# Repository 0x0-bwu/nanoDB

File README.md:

# nanoDB

A lightweight, high-performance database framework designed for Electronic Design Automation (EDA) applications.

**Status:** Under Active Development  
**License:** Non-commercial

## Overview

nanoDB is a modern C++ database framework specifically built for EDA workflows. It provides efficient data structures and interfaces for managing chip design data, including Liberty timing libraries, Verilog netlists, parasitic information, package models, and power analysis.

## Features

- **Liberty Library Support**: Parse and manage Liberty timing library files (.lib)
- **Verilog Support**: Handle Verilog netlist data structures
- **Chip Design Data**: Comprehensive chip design database with efficient storage
- **Package Modeling**: Support for package design and analysis
- **Parasitic Analysis**: Manage parasitic resistance and capacitance data
- **Power Analysis**: Power consumption calculation and optimization
- **Serialization**: Boost serialization support for database persistence
- **Thread-Safe**: Multi-threaded operations support with OpenMP
- **Memory Efficiency**: Optional jemalloc/tcmalloc support for optimized memory management

## Requirements

### System Requirements
- CMake 3.14 or higher
- C++23 compatible compiler:
  - GCC (recommended)
  - AppleClang (macOS)

### Dependencies

- **Boost** (1.83.0 or higher)
  - boost_serialization
- **Eigen3**: Linear algebra library
- **libpng**: PNG image support
- **OpenMP**: Parallel computing (optional)
- **jemalloc** or **tcmalloc**: Memory allocator (optional)

### Environment Variables

Set the `BOOST_PATH` environment variable to your Boost installation directory:
```bash
export BOOST_PATH=/path/to/boost
```

For custom Eigen installation, set:
```bash
export EIGEN_PATH=/path/to/eigen
```

## Building

### Basic Build

```bash
# Configure
cmake -Bbuild -G Ninja

# Build
cmake --build build
```

### Build Options

```bash
# Enable assertions
cmake -Bbuild -DENABLE_ASSERTION=ON

# Enable/disable exceptions
cmake -Bbuild -DENABLE_EXCEPTION=OFF

# Use jemalloc
cmake -Bbuild -DNS_MALLOC_LIB=jemalloc

# Use tcmalloc
cmake -Bbuild -DNS_MALLOC_LIB=tcmalloc

# Enable address sanitizer (for debugging)
cmake -Bbuild -DENABLE_ASAN=ON

# Enable thread sanitizer (for debugging)
cmake -Bbuild -DENABLE_TSAN=ON

# Enable profiling
cmake -Bbuild -DENABLE_PROFILING=ON

# Build without tests
cmake -Bbuild -DBUILD_NANO_TEST=OFF
```

### macOS Build

On macOS with Homebrew:
```bash
# Install dependencies
brew install boost eigen libpng cmake ninja

# Optional: Enable Apple Accelerate framework
cmake -Bbuild -DENABLE_APPLE_ACCELERATE=ON -G Ninja
cmake --build build
```

### Ubuntu/Debian Build

```bash
# Install dependencies
sudo apt-get update
sudo apt-get install build-essential cmake ninja-build \
    libeigen3-dev libpng-dev libjemalloc-dev

# Install Boost (or use install-boost action in CI)
# Build with jemalloc
export BOOST_PATH=/path/to/boost
cmake -Bbuild -DNS_MALLOC_LIB=jemalloc -G Ninja
cmake --build build
```

## Testing

Run the unit tests:
```bash
build/bin/nanoTest.exe
```

## Project Structure

```
nanoDB/
├── include/nano/          # Public headers
│   ├── db                 # Main database header
│   ├── core/              # Core module headers
│   │   ├── basic/         # Basic data structures
│   │   ├── chip/          # Chip design data
│   │   ├── liberty/       # Liberty library
│   │   ├── package/       # Package modeling
│   │   ├── parasitic/     # Parasitic data
│   │   ├── power/         # Power analysis
│   │   └── verilog/       # Verilog support
│   └── common/            # Common utilities
├── src/                   # Source code implementation
│   ├── basic/             # Database core implementation
│   ├── chip/              # Chip module
│   ├── liberty/           # Liberty parser and data structures
│   ├── package/           # Package module
│   ├── parasitic/         # Parasitic module
│   ├── power/             # Power module
│   └── verilog/           # Verilog module
├── test/                  # Unit tests
├── 3rdparty/             # Third-party dependencies
├── reference/            # Reference documentation
└── tools/                # Utility tools
```

## Usage

Include the main header in your C++ code:

```cpp
#include <nano/db>

// Use the nano namespace
using namespace nano;

// Create and use database objects
// (Detailed API documentation coming soon)
```

## Contributing

This project is currently under active development. Contributions, issues, and feature requests are welcome.

## License

**Non-commercial use only.** This software is provided for educational and research purposes.

## References

- Liberty User Guides and Reference Manual Suite (Version 2017.06) included in `reference/` directory

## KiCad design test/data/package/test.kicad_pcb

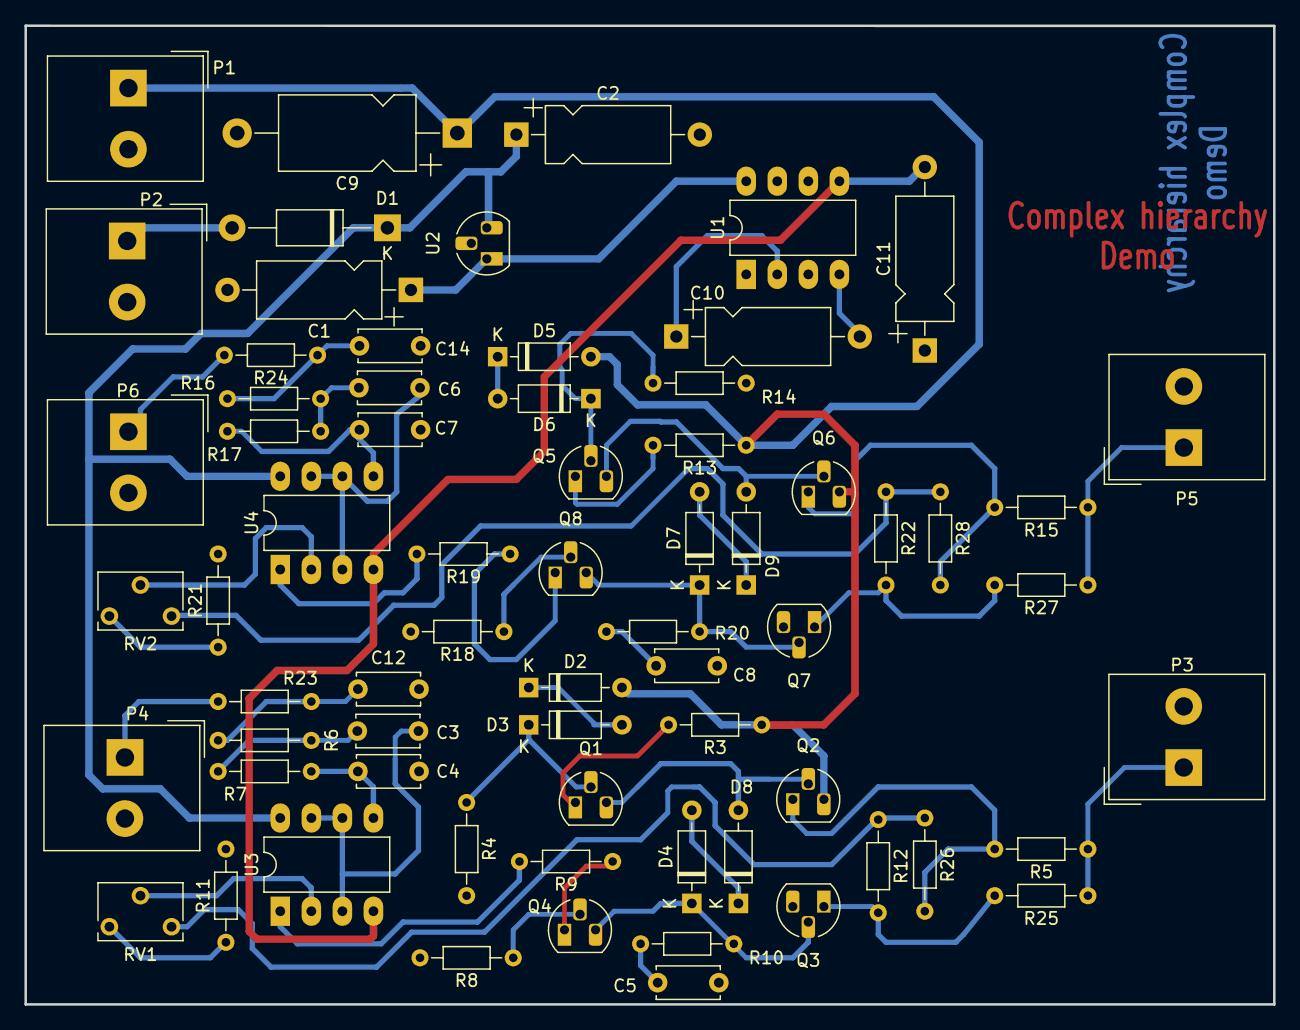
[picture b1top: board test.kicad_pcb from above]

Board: 2 copper layers, 102.1 x 80.0 mm, 68 parts (0 on the bottom side), 50 nets.

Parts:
C1: 47uF; CP_Axial_L10.0mm_D4.5mm_P15.00mm_Horizontal
C2: 47uF/20V; CP_Axial_L10.0mm_D4.5mm_P15.00mm_Horizontal
C3, C6: 15nF; C_Disc_D5.0mm_W2.5mm_P5.00mm
C4, C7: 4.7nF; C_Disc_D5.0mm_W2.5mm_P5.00mm
C5, C8: 820pF; C_Disc_D5.0mm_W2.5mm_P5.00mm
C9: 47uF/63V; CP_Axial_L11.0mm_D6.0mm_P18.00mm_Horizontal
C10, C11: 10uF; CP_Axial_L10.0mm_D4.5mm_P15.00mm_Horizontal
C12, C14: 150nF; C_Disc_D5.0mm_W2.5mm_P5.00mm
D1: 1N4007; D_DO-41_SOD81_P12.70mm_Horizontal
D2, D3, D4, D5, D6, D7, D8, D9: 1N4148; D_DO-35_SOD27_P7.62mm_Horizontal
P1, P2, P3, P4, P5, P6: CONN_2; Altech_AK300_1x02_P5.00mm_45-Degree
Q1, Q3, Q5, Q7: MPSA92; TO-92_HandSolder
Q2, Q4, Q6, Q8: MPSA42; TO-92_HandSolder
R3, R13: 470; R_Axial_DIN0204_L3.6mm_D1.6mm_P7.62mm_Horizontal
R4, R12, R14, R22, R26, R28: 220K; R_Axial_DIN0204_L3.6mm_D1.6mm_P7.62mm_Horizontal
R5, R15, R25, R27: 47; R_Axial_DIN0204_L3.6mm_D1.6mm_P7.62mm_Horizontal
R6, R7, R16, R17: 22K; R_Axial_DIN0204_L3.6mm_D1.6mm_P7.62mm_Horizontal
R8, R9, R18, R19, R23, R24: 1K; R_Axial_DIN0204_L3.6mm_D1.6mm_P7.62mm_Horizontal
R10, R20: 5,6K; R_Axial_DIN0204_L3.6mm_D1.6mm_P7.62mm_Horizontal
R11, R21: 4,7K; R_Axial_DIN0204_L3.6mm_D1.6mm_P7.62mm_Horizontal
RV1, RV2: 4,7K; Potentiometer_Bourns_3266W_Vertical
U1: ICL7660; DIP-8_W7.62mm_LongPads
U2: 78L05; TO-92_HandSolder
U3, U4: LM358N; DIP-8_W7.62mm_LongPads

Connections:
+12V: C2.1, D1.1 (K), U2.3 (VI), U3.8 (V+), U4.8 (V+)
-VAA: C11.2, U1.5 (VOUT), U3.4 (V-), U4.4 (V-)
/12Vext: D1.2 (A), P2.1
/ampli_ht_horizontal/PIEZO_IN: P6.1, R24.2
/ampli_ht_horizontal/PIEZO_OUT: P5.1, R15.1, R27.1
/ampli_ht_horizontal/S_OUT+: R22.1, R28.1, RV2.3
/ampli_ht_horizontal/Vpil_0_3,3V: C6.1, U4.3 (+), U4.6 (-), U4.7
/ampli_ht_vertical/PIEZO_IN: P4.1, R23.2
/ampli_ht_vertical/PIEZO_OUT: P3.1, R5.1, R25.1
/ampli_ht_vertical/S_OUT+: R12.1, R26.1, RV1.3
/ampli_ht_vertical/Vpil_0_3,3V: C3.1, U3.3 (+), U3.6 (-), U3.7
GND: C1.2, C2.2, C4.2, C5.2, C7.2, C8.2, C9.2, C11.1, C12.2, C14.2, P1.2 (PM), P2.2 (PM), P3.2 (PM), P4.2 (PM), P5.2 (PM), P6.2 (PM), Q3.3 (C), Q7.3 (C), R4.2, R8.2, R11.2, R14.2, R18.2, R21.2, U1.3 (GND), U2.2 (GND)
HT: C9.1, D2.2 (A), D5.2 (A), P1.1, Q2.3 (C), Q6.3 (C), R3.1, R13.1
unnamed: C3.2, R6.1, R7.2
unnamed: C5.1, R10.2
unnamed: C6.2, R16.1, R17.2
unnamed: C8.1, R20.2
unnamed: C12.1, R6.2, R23.1
unnamed: C14.1, R16.2, R24.1
unnamed: D2.1 (K), D3.2 (A)
unnamed: D3.1 (K), Q1.2 (B), R4.1
unnamed: D4.2 (A), D8.1 (K)
unnamed: D4.1 (K), Q3.2 (B), Q4.3 (C), R10.1
unnamed: D5.1 (K), D6.2 (A)
unnamed: D6.1 (K), Q5.2 (B), R14.1
unnamed: D7.2 (A), D9.1 (K)
unnamed: D7.1 (K), Q7.2 (B), Q8.3 (C), R20.1
unnamed: D8.2 (A), Q1.3 (C), Q2.2 (B)
unnamed: D9.2 (A), Q5.3 (C), Q6.2 (B)
unnamed: Q1.1 (E), R3.2
unnamed: Q2.1 (E), R5.2, R26.2
unnamed: Q3.1 (E), R12.2, R25.2
unnamed: Q4.2 (B), R8.1
unnamed: Q4.1 (E), R9.1
unnamed: Q5.1 (E), R13.2
unnamed: Q6.1 (E), R15.2, R28.2
unnamed: Q7.1 (E), R22.2, R27.2
unnamed: Q8.2 (B), R18.1
unnamed: Q8.1 (E), R19.1
unnamed: R9.2, U3.1
unnamed: R11.1, RV1.1
unnamed: R19.2, U4.1
unnamed: R21.1, RV2.1
unnamed: C10.1, U1.2 (CAP+)
unnamed: C10.2, U1.4 (CAP-)
unnamed: RV1.2, U3.2 (-)
unnamed: C4.1, R7.1, U3.5 (+)
unnamed: RV2.2, U4.2 (-)
unnamed: C7.1, R17.1, U4.5 (+)
VCC: C1.1, U1.8 (V+), U2.1 (VO)

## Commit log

2024-12-29 impl: add exists module
2024-12-29 impl: add workflow
2024-12-30 impl: database
2024-12-30 impl: common::material
2024-12-30 impl: add Id<T> downcase operator --
2024-12-30 impl: remove namespace common, add package layout
2024-12-31 fix: implicit/explicit id convertion
2024-12-31 impl: wrapper lut args to luts
2024-12-31 allow implicit id conversion from derived to base
2024-12-31 impl: id convertion and test
2024-12-31 impl: fix potential issue
2024-12-31 impl: shape and transform
2025-01-01 impl: package
2025-01-02 impl: package, cellinst
2025-01-02 impl: package::cellinst
2025-01-03 impl: const id type
2025-01-03 impl: refine cid
2025-01-03 impl: remove id alias
2025-01-04 impl: package::Component, Clonable
2025-01-05 impl: shared clone and unique clone
2025-01-05 impl: id container iterator
2025-01-05 impl: inherit package from footprint cell
2025-01-05 impl: interface, component layer
2025-01-05 rename: package::interface -> package::footprint
2025-01-05 impl: package, bondwire connection
2025-01-06 fix: serialization assert fail due to bool variable not initialized
2025-01-06 test: package setup design
2025-01-06 impl: enhance IdIterator with derived type
2025-01-06 impl: package flatten
2025-01-07 impl: simplify
2025-01-07 impl: package clone
2025-01-08 fix: type
2025-01-08 impl: IdVec::Clone
2025-01-08 update: rename function name, remove compile warning
2025-01-08 impl: clone
2025-01-09 rftr: alias and enable_if replacement
2025-01-10 impl: add destroy function
2025-01-10 fix: typo
2025-01-10 update: include
2025-01-11 impl: package layout retriever
2025-01-12 impl: power and lookup table, package layout retriever
2025-01-13 update: include path
2025-01-13 fix: xml serialization issue due to un-innitialized memebers
2025-01-13 fix: compile error
2025-01-14 rftr: add pod type default initializer; make default constructor private; remove id recycler
2025-01-14 impl: package bonding wire retriever
2025-01-15 impl: find function and package apis
2025-01-16 impl: update FindAll function
2025-01-16 impl: enable lut lazy evaluated
2025-01-17 fix: some bugs
2025-01-17 fix: incorrect assertion
2025-01-18 update: alias std::vector->Vec
2025-01-18 update: alias
2025-01-18 fix: test case setup error
2025-01-18 fix: clone bug
2025-01-19 impl: add api
2025-01-23 fix: remove serialiation compile warning in gcc
2025-01-23 rftr: save/load function
2025-01-24 impl: checksum; move to cxx23
2025-01-24 impl: hash function
2025-01-25 impl: change default circle div 32->16
2025-01-27 impl: package kicad extension
2025-01-27 impl: kicad parser
2025-01-28 impl: package layout render
2025-01-29 impl: kicad parser; update: vec alias
2025-01-30 impl: kicad parser, component
2025-02-01 pfix: kicad comp parser
2025-02-01 fix: kicad comp parser
2025-02-02 impl: kicad parser, pad
2025-02-03 impl: kicad parser, stackup layer
2025-02-04 impl: kicad parser, padstack
2025-02-04 impl: kicad parser, via
2025-02-05 impl: shape oval, kicad parser, pad
2025-02-06 fix: PadstackInst clone not copy transform issue; alias update
2025-02-06 imp: material prop lut
2025-02-06 fix: set bonding wire material
2025-02-06 impl: nano log; fix: entity copy; impl: lut and material function
2025-02-07 rftr: binding clone; update: test case
2025-02-07 update: 3rdparty
2025-02-08 impl: polygon merge
2025-02-08 impl: add apis
2025-02-09 fix: hana structure init issue; rftr: current dir
2025-02-10 fix: thread pool usage(tmp)
2025-02-13 fix: crash when implicit convert invalid base
2025-02-13 impl: add layout elevation,thickness query api; update: test case
2025-02-14 impl: add reset in iter; update: alias and test case
2025-02-22 frtr: invalid function
2025-02-23 fix: namespace conflict with apple accelerate
2025-02-26 fix: set current dir bug
2025-03-01 update: add test case
2025-03-01 fix: padstack missing in package; impl: set mat in padstack
2025-04-02 fix: different global var w/o #pragma once
2025-04-02 fix: via singleton
2025-05-24 fix: w/a boost compiling error with macOS 15.4
2025-05-24 impl: package edit
2025-10-23 Initial plan
2025-10-23 Add comprehensive unit tests for common, chip, and liberty modules
2025-10-23 Add power module and enhanced archive serialization tests
2025-10-23 Add comprehensive edge case tests and test coverage documentation
2025-10-28 Fix three bugs: missing return, wrong unit mapping, and double insertion
2025-10-28 Final verification complete - all bugs fixed
2025-11-17 update words
2025-11-17 fix: build error
2025-11-17 impl: unify Id and CId
2025-11-18 Update README.md with comprehensive documentation
2025-11-18 Optimize string and vector parameters - pass by const reference
2025-11-18 Fix additional loop inefficiencies and optimize string operations
2025-11-18 Complete performance optimization analysis and documentation
2025-11-18 perf: copy issue
2025-11-18 Initial exploration and bug discovery
2025-11-18 Fix: Correct FF (femtofarad) capacitance unit mapping
    The capacitance unit "FF" was incorrectly mapped to PF (picofarad)
    instead of FF (femtofarad) in ParseCapUnit function. This caused
    incorrect capacitance conversions when parsing Liberty files with
    femtofarad units.
    Fixed by changing line 40 from:
    ("FF", CapUnit::Unit::PF)
2025-11-18 Final verification and documentation
2025-11-18 Clean up: Remove CodeQL build artifacts and update .gitignore
2025-11-18 fix: create pkg with mab lib
2025-11-19 Initial plan for fixing memory leak
2025-11-19 Fix memory leak in NSPackagePadstack.cpp
2025-11-19 Fix memory leak in Padstack shape getter methods
2025-11-19 update: alias; fix: typo
2025-11-24 impl: add sync script
2025-12-15 fix: dependency
2025-12-15 update: lib name
2026-01-08 impl: liberty set
